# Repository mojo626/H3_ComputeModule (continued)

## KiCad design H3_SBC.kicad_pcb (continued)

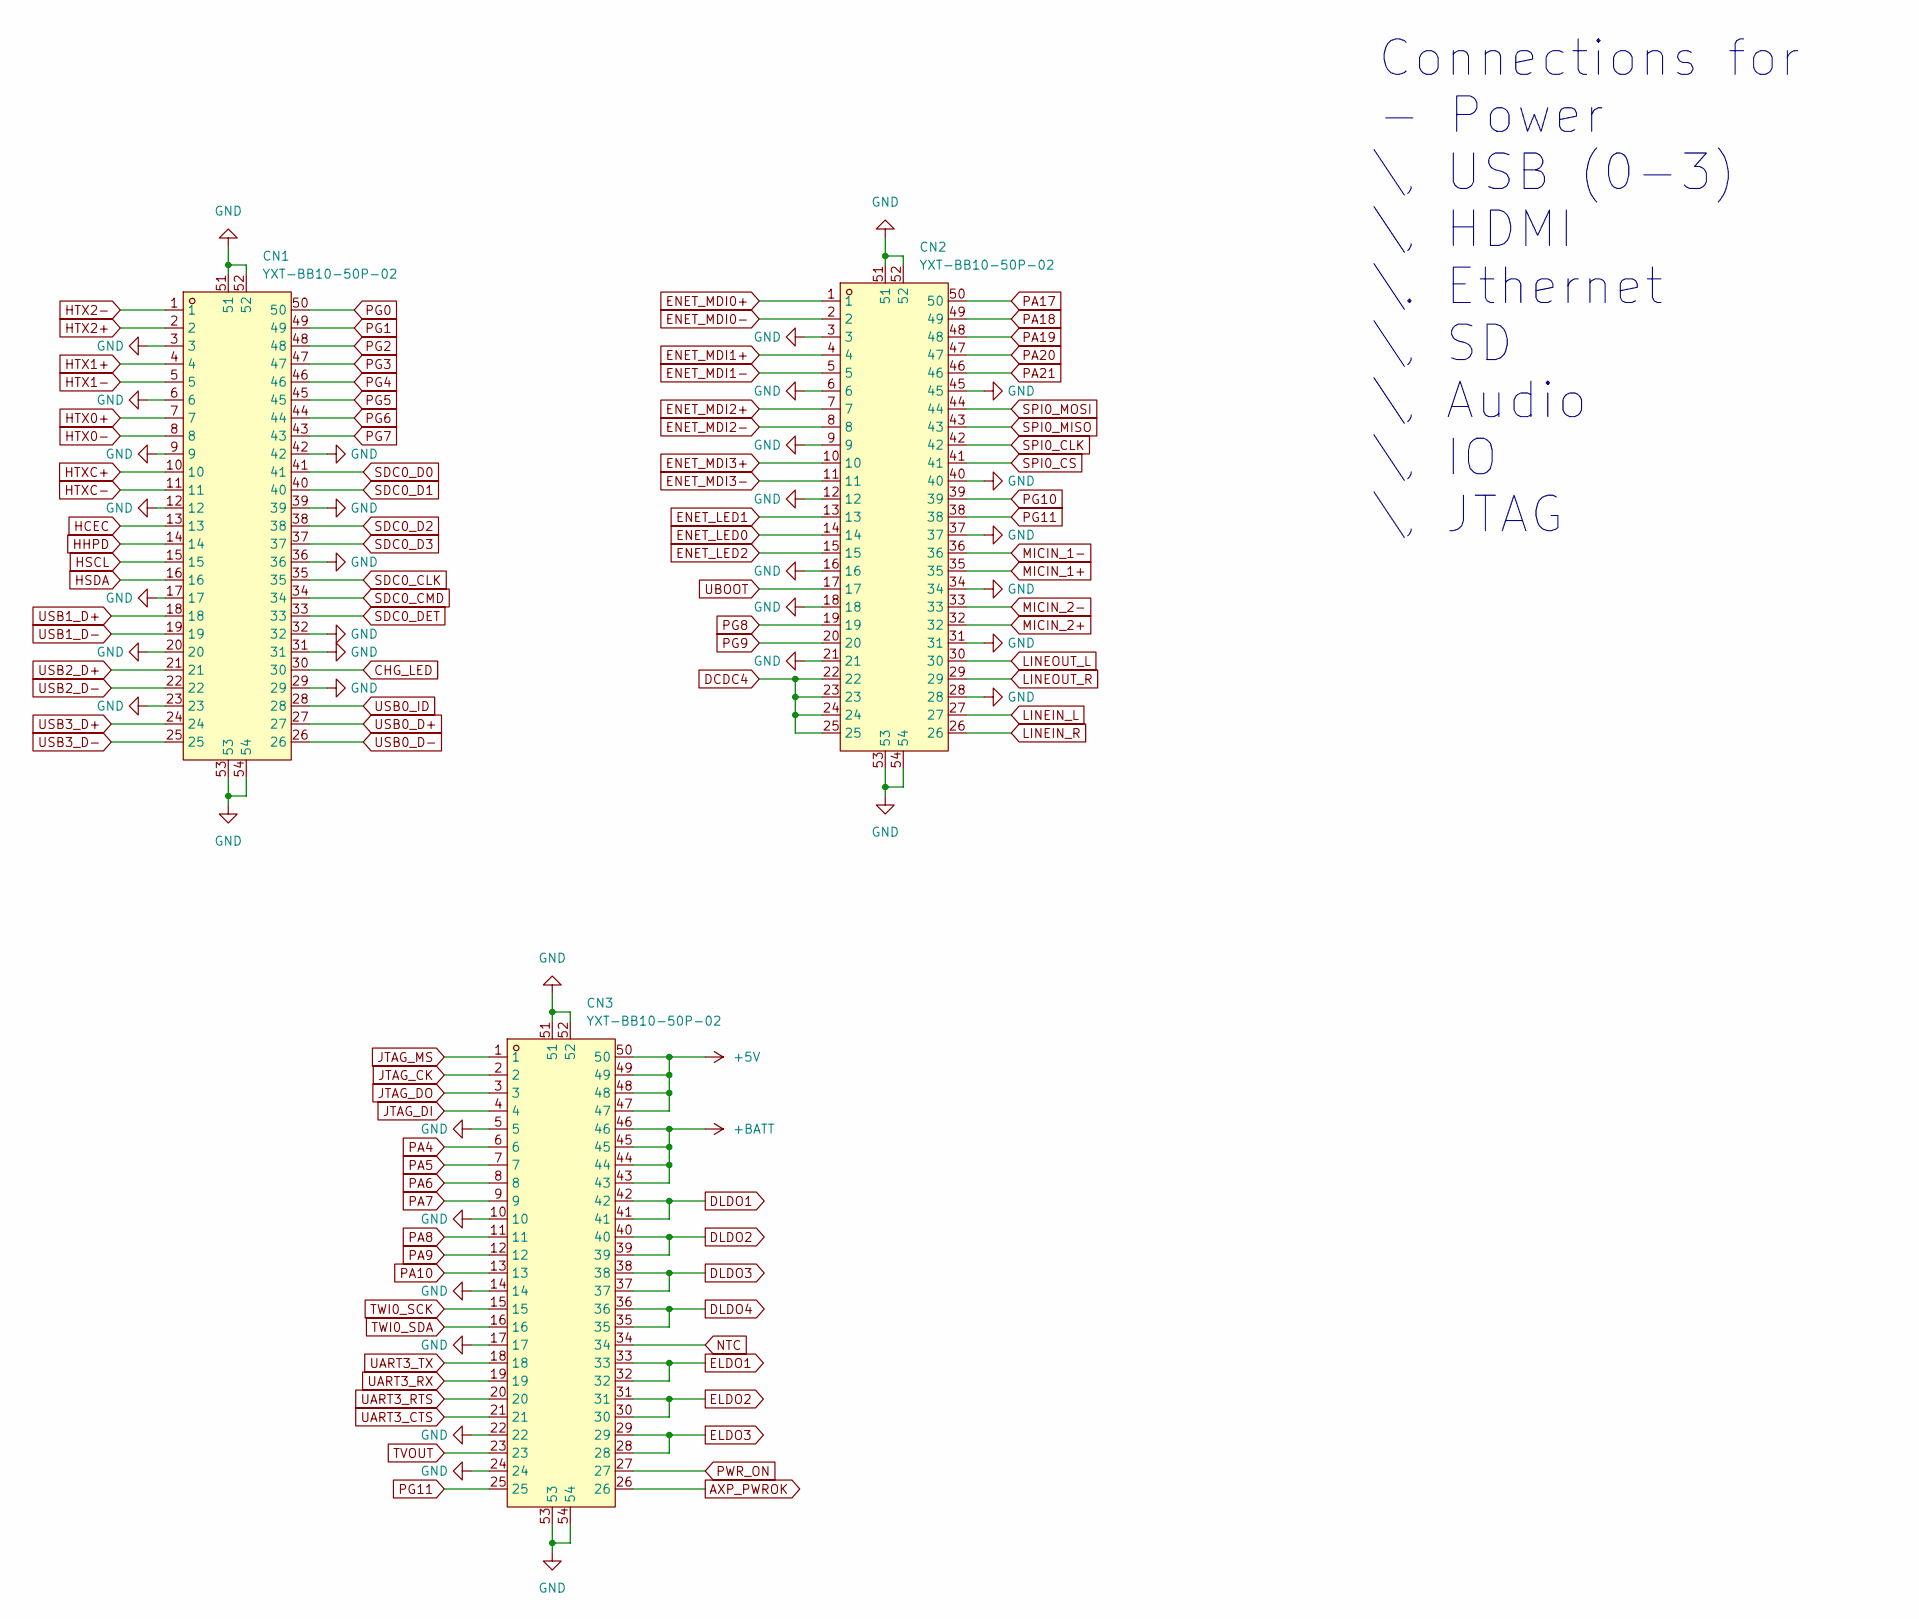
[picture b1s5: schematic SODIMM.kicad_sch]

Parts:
CN1, CN2, CN3: YXT-BB10-50P-02; CONN-SMD_YXT-BB10-50P-02; LCSC Part C2763977

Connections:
+5V: CN3.47, CN3.48, CN3.49, CN3.50; also elsewhere on the board
+BATT: CN3.43, CN3.44, CN3.45, CN3.46; also elsewhere on the board
AXP_PWROK: CN3.26; also elsewhere on the board
CHG_LED: CN1.30; also elsewhere on the board
DCDC4: CN2.22, CN2.23, CN2.24, CN2.25; also elsewhere on the board
DLDO1: CN3.41, CN3.42; also elsewhere on the board
DLDO2: CN3.39, CN3.40; also elsewhere on the board
DLDO3: CN3.37, CN3.38; also elsewhere on the board
DLDO4: CN3.35, CN3.36; also elsewhere on the board
ELDO1: CN3.32, CN3.33; also elsewhere on the board
ELDO2: CN3.30, CN3.31; also elsewhere on the board
ELDO3: CN3.28, CN3.29; also elsewhere on the board
ENET_LED0: CN2.14; also elsewhere on the board
ENET_LED1: CN2.13; also elsewhere on the board
ENET_LED2: CN2.15; also elsewhere on the board
ENET_MDI0+: CN2.1; also elsewhere on the board
ENET_MDI0-: CN2.2; also elsewhere on the board
ENET_MDI1+: CN2.4; also elsewhere on the board
ENET_MDI1-: CN2.5; also elsewhere on the board
ENET_MDI2+: CN2.7; also elsewhere on the board
ENET_MDI2-: CN2.8; also elsewhere on the board
ENET_MDI3+: CN2.10; also elsewhere on the board
ENET_MDI3-: CN2.11; also elsewhere on the board
GND: CN1.3, CN1.6, CN1.9, CN1.12, CN1.17, CN1.20, CN1.23, CN1.29, CN1.31, CN1.32, CN1.36, CN1.39, CN1.42, CN1.51, CN1.52, CN1.53, CN1.54, CN2.3, CN2.6, CN2.9, CN2.12, CN2.16, CN2.18, CN2.21, CN2.28, CN2.31, CN2.34, CN2.37, CN2.40, CN2.45, CN2.51, CN2.52, CN2.53, CN2.54, CN3.5, CN3.10, CN3.14, CN3.17, CN3.22, CN3.24, CN3.51, CN3.52, CN3.53, CN3.54; also elsewhere on the board
HCEC: CN1.13; also elsewhere on the board
HHPD: CN1.14; also elsewhere on the board
HSCL: CN1.15; also elsewhere on the board
HSDA: CN1.16; also elsewhere on the board
HTX0+: CN1.7; also elsewhere on the board
HTX0-: CN1.8; also elsewhere on the board
HTX1+: CN1.4; also elsewhere on the board
HTX1-: CN1.5; also elsewhere on the board
HTX2+: CN1.2; also elsewhere on the board
HTX2-: CN1.1; also elsewhere on the board
HTXC+: CN1.10; also elsewhere on the board
HTXC-: CN1.11; also elsewhere on the board
JTAG_CK: CN3.2; also elsewhere on the board
JTAG_DI: CN3.4; also elsewhere on the board
JTAG_DO: CN3.3; also elsewhere on the board
JTAG_MS: CN3.1; also elsewhere on the board
LINEIN_L: CN2.27; also elsewhere on the board
LINEIN_R: CN2.26; also elsewhere on the board
LINEOUT_L: CN2.30; also elsewhere on the board
LINEOUT_R: CN2.29; also elsewhere on the board
MICIN_1+: CN2.35; also elsewhere on the board
MICIN_1-: CN2.36; also elsewhere on the board
MICIN_2+: CN2.32; also elsewhere on the board
MICIN_2-: CN2.33; also elsewhere on the board
NTC: CN3.34; also elsewhere on the board
PA4: CN3.6; also elsewhere on the board
PA5: CN3.7; also elsewhere on the board
PA6: CN3.8; also elsewhere on the board
PA7: CN3.9; also elsewhere on the board
PA8: CN3.11; also elsewhere on the board
PA9: CN3.12; also elsewhere on the board
PA10: CN3.13; also elsewhere on the board
PA17: CN2.50; also elsewhere on the board
PA18: CN2.49; also elsewhere on the board
PA19: CN2.48; also elsewhere on the board
PA20: CN2.47; also elsewhere on the board
PA21: CN2.46; also elsewhere on the board
PG0: CN1.50; also elsewhere on the board
PG1: CN1.49; also elsewhere on the board
PG2: CN1.48; also elsewhere on the board
PG3: CN1.47; also elsewhere on the board
PG4: CN1.46; also elsewhere on the board
PG5: CN1.45; also elsewhere on the board
PG6: CN1.44; also elsewhere on the board
PG7: CN1.43; also elsewhere on the board
PG8: CN2.19; also elsewhere on the board
PG9: CN2.20; also elsewhere on the board
PG10: CN2.39; also elsewhere on the board
PG11: CN2.38, CN3.25; also elsewhere on the board
PWR_ON: CN3.27; also elsewhere on the board
SDC0_CLK: CN1.35; also elsewhere on the board
SDC0_CMD: CN1.34; also elsewhere on the board
SDC0_D0: CN1.41; also elsewhere on the board
SDC0_D1: CN1.40; also elsewhere on the board
SDC0_D2: CN1.38; also elsewhere on the board
SDC0_D3: CN1.37; also elsewhere on the board
SDC0_DET: CN1.33; also elsewhere on the board
SPI0_CLK: CN2.42; also elsewhere on the board
SPI0_CS: CN2.41; also elsewhere on the board
SPI0_MISO: CN2.43; also elsewhere on the board
SPI0_MOSI: CN2.44; also elsewhere on the board
TVOUT: CN3.23; also elsewhere on the board
TWI0_SCK: CN3.15; also elsewhere on the board
TWI0_SDA: CN3.16; also elsewhere on the board
UART3_CTS: CN3.21; also elsewhere on the board
UART3_RTS: CN3.20; also elsewhere on the board
UART3_RX: CN3.19; also elsewhere on the board
UART3_TX: CN3.18; also elsewhere on the board
UBOOT: CN2.17; also elsewhere on the board
USB0_D+: CN1.27; also elsewhere on the board
USB0_D-: CN1.26; also elsewhere on the board
USB0_ID: CN1.28; also elsewhere on the board
USB1_D+: CN1.18; also elsewhere on the board
USB1_D-: CN1.19; also elsewhere on the board
USB2_D+: CN1.21; also elsewhere on the board
USB2_D-: CN1.22; also elsewhere on the board
USB3_D+: CN1.24; also elsewhere on the board
USB3_D-: CN1.25; also elsewhere on the board

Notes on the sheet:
Connections for - Power \, USB (0-3) \, HDMI \. Ethernet \, SD \, Audio \, IO \, JTAG

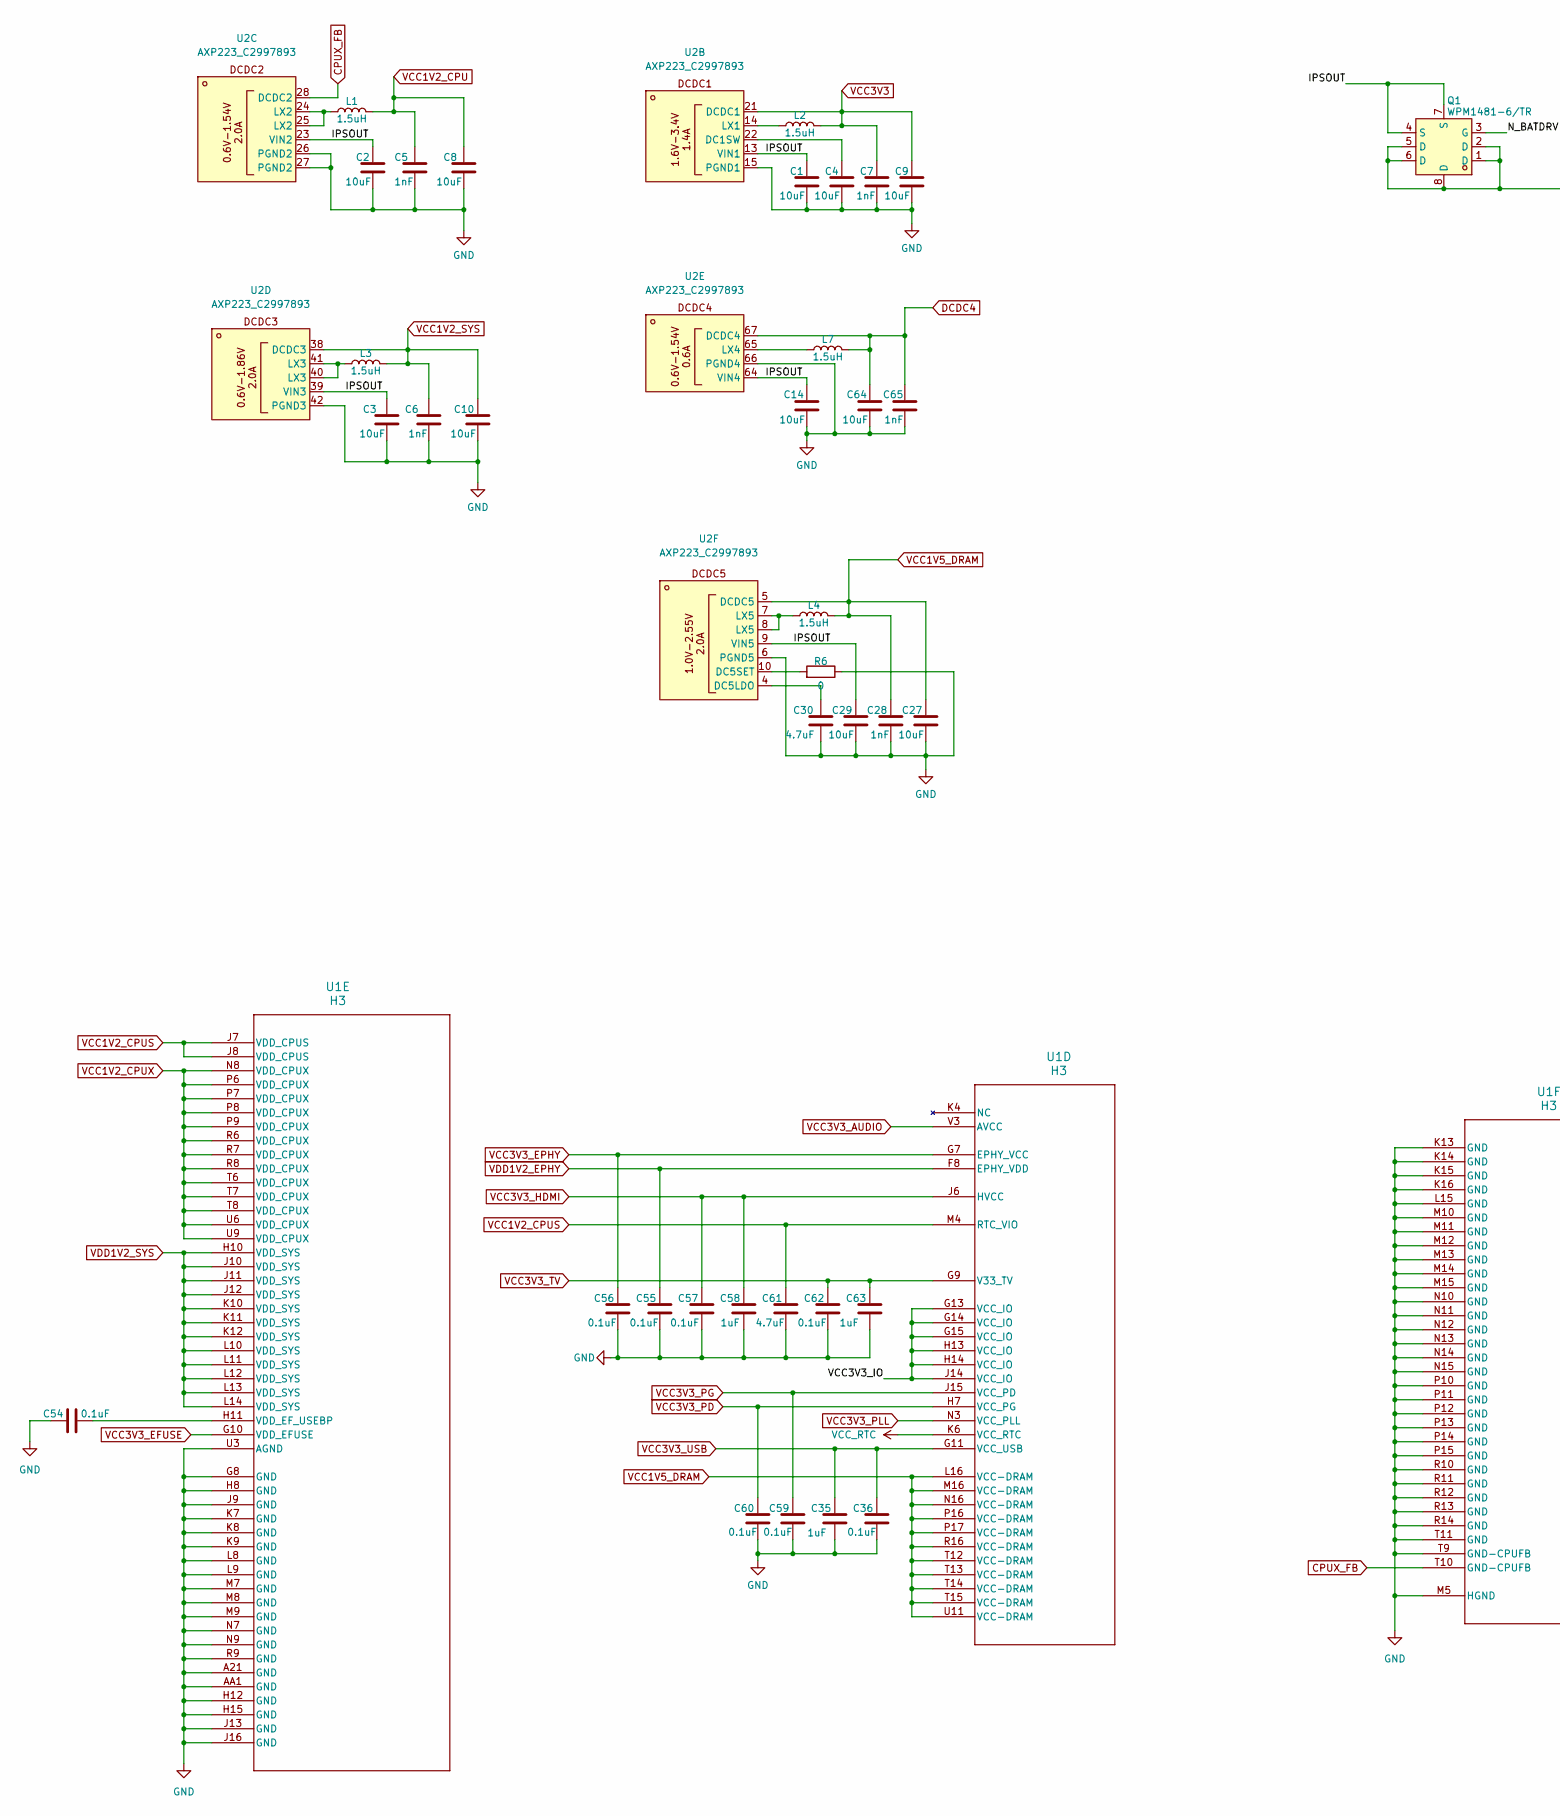
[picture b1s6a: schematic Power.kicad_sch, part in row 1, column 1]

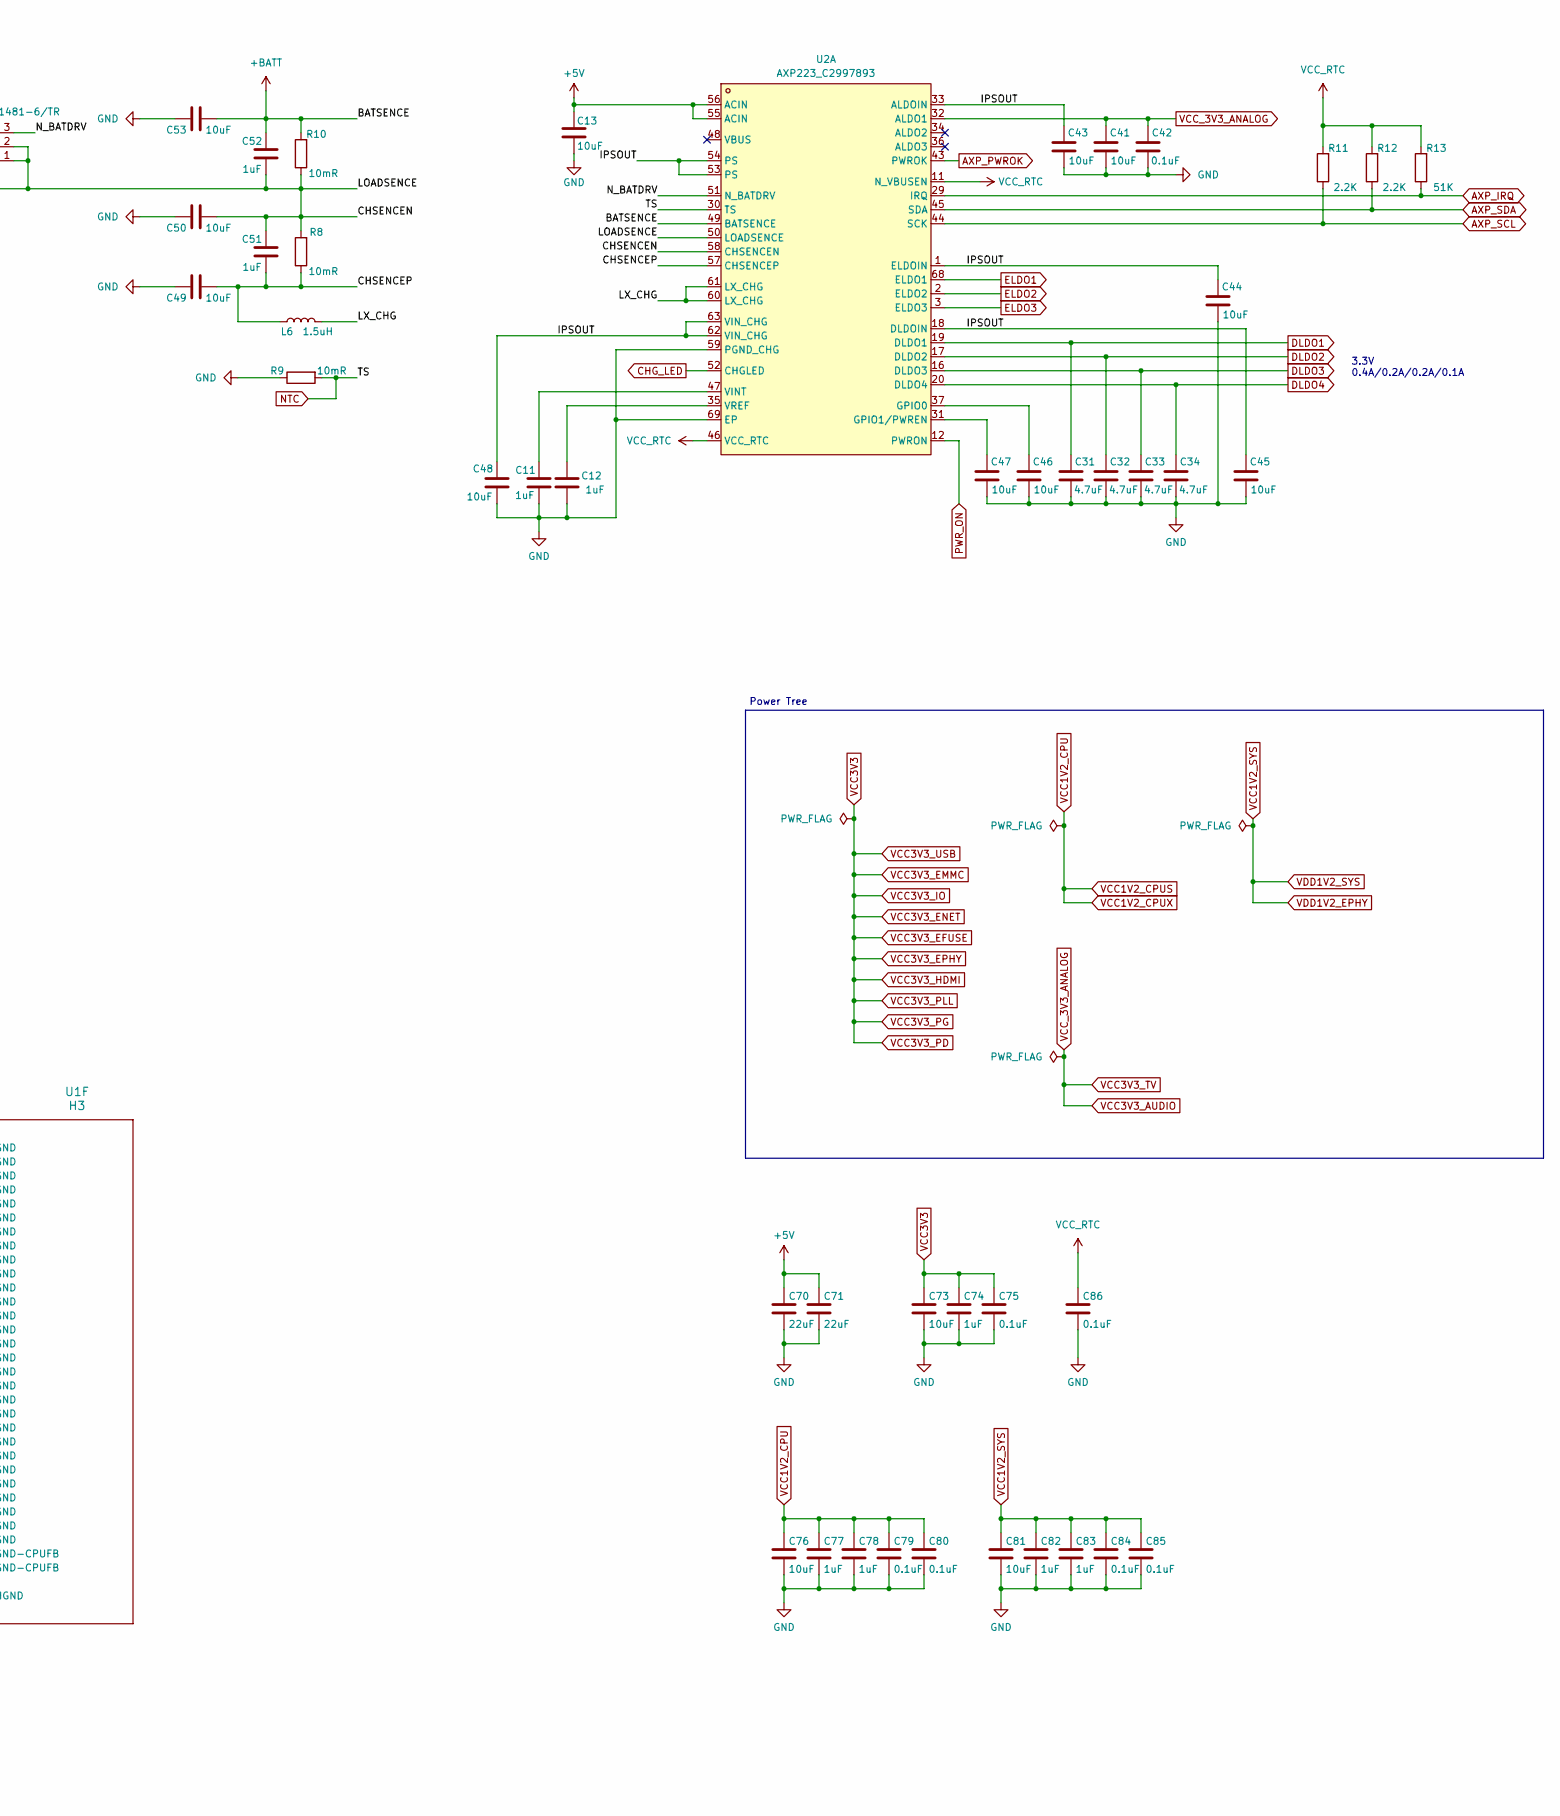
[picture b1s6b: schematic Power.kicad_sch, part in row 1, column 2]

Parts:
C1, C2, C3, C4, C8, C9, C10, C13, C14, C27, C29, C41, C43, C44, C45, C46, C47, C48, C49, C50, C53, C64, C73, C76, C81: 10uF; C_0402_1005Metric
C5, C6, C7, C28, C65: 1nF; C_0402_1005Metric
C11, C12, C35, C51, C52, C58, C63, C74, C77, C78, C82, C83: 1uF; C_0402_1005Metric
C30, C31, C32, C33, C34, C61: 4.7uF; C_0402_1005Metric
C36, C42, C54, C55, C56, C57, C59, C60, C62, C75, C79, C80, C84, C85, C86: 0.1uF; C_0402_1005Metric
C70, C71: 22uF; C_0603_1608Metric
L1, L2, L3, L4, L6, L7: 1.5uH; L_0402_1005Metric
Q1: WPM1481-6/TR; DFN-6L_L2.0-W2.0-P0.65-BL_WPM1481-6; LCSC Part C239798
R6: 0; R_0402_1005Metric
R8, R9, R10: 10mR; R_0402_1005Metric
R11, R12: 2.2K; R_0402_1005Metric
R13: 51K; R_0402_1005Metric
U1: H3; BGA-347_L14.0-W14.0-R21-C21-P0.65-TL
U2: AXP223_C2997893; QFN-68_L8.0-W8.0-P0.40-TL-EP5.7; LCSC Part C2997893

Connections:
+5V: C13.1, C70.1, C71.1, U2.55 (ACIN), U2.56 (ACIN); also elsewhere on the board
+BATT: C52.2, C53.1, R10.2, U2.49 (BATSENCE); also elsewhere on the board
/Power/CHSENCEN: C50.1, C51.2, C52.1, Q1.1 (D), Q1.2 (D), Q1.5 (D), Q1.6 (D), Q1.8 (D), R8.2, R10.1, U2.50 (LOADSENCE), U2.58 (CHSENCEN)
/Power/CHSENCEP: C49.2, C51.1, L6.1, R8.1, U2.57 (CHSENCEP)
/Power/IPSOUT: C1.2, C2.2, C3.2, C14.2, C29.2, C43.2, C44.2, C45.2, C48.2, Q1.4 (S), Q1.7 (S), U2.1 (ELDOIN), U2.9 (VIN5), U2.13 (VIN1), U2.18 (DLDOIN), U2.23 (VIN2), U2.33 (ALDOIN), U2.39 (VIN3), U2.53 (PS), U2.54 (PS), U2.62 (VIN_CHG), U2.63 (VIN_CHG), U2.64 (VIN4)
/Power/LX_CHG: L6.2, U2.60 (LX_CHG), U2.61 (LX_CHG)
/Power/N_BATDRV: Q1.3 (G), U2.51 (N_BATDRV)
AXP_IRQ: R13.1, U2.29 (IRQ); also elsewhere on the board
AXP_PWROK: U2.43 (PWROK); also elsewhere on the board
AXP_SCL: R11.1, U2.44 (SCK); also elsewhere on the board
AXP_SDA: R12.1, U2.45 (SDA); also elsewhere on the board
CHG_LED: U2.52 (CHGLED); also elsewhere on the board
CPUX_FB: U1.T10 (GND-CPUFB), U2.28 (DCDC2)
DCDC4: C64.2, C65.2, L7.2, U2.67 (DCDC4); also elsewhere on the board
DLDO1: C31.2, U2.19 (DLDO1); also elsewhere on the board
DLDO2: C32.2, U2.17 (DLDO2); also elsewhere on the board
DLDO3: C33.2, U2.16 (DLDO3); also elsewhere on the board
DLDO4: C34.2, U2.20 (DLDO4); also elsewhere on the board
ELDO1: U2.68 (ELDO1); also elsewhere on the board
ELDO2: U2.2 (ELDO2); also elsewhere on the board
ELDO3: U2.3 (ELDO3); also elsewhere on the board
GND: C1.1, C2.1, C3.1, C4.1, C5.1, C6.1, C7.1, C8.1, C9.1, C10.1, C11.2, C12.1, C13.2, C14.1, C27.1, C28.1, C29.1, C30.1, C31.1, C32.1, C33.1, C34.1, C35.1, C36.1, C41.1, C42.1, C43.1, C44.1, C45.1, C46.1, C47.1, C48.1, C49.1, C50.2, C53.2, C54.1, C55.1, C56.1, C57.1, C58.1, C59.1, C60.1, C61.1, C62.1, C63.1, C64.1, C65.1, C70.2, C71.2, C73.2, C74.2, C75.2, C76.2, C77.2, C78.2, C79.2, C80.2, C81.2, C82.2, C83.2, C84.2, C85.2, C86.2, R6.1, R9.1, U1.A21 (GND), U1.AA1 (GND), U1.G8 (GND), U1.H8 (GND), U1.H12 (GND), U1.H15 (GND), U1.J9 (GND), U1.J13 (GND), U1.J16 (GND), U1.K7 (GND), U1.K8 (GND), U1.K9 (GND), U1.K13 (GND), U1.K14 (GND), U1.K15 (GND), U1.K16 (GND), U1.L8 (GND), U1.L9 (GND), U1.L15 (GND), U1.M5 (HGND), U1.M7 (GND), U1.M8 (GND), U1.M9 (GND), U1.M10 (GND), U1.M11 (GND), U1.M12 (GND), U1.M13 (GND), U1.M14 (GND), U1.M15 (GND), U1.N7 (GND), U1.N9 (GND), U1.N10 (GND), U1.N11 (GND), U1.N12 (GND), U1.N13 (GND), U1.N14 (GND), U1.N15 (GND), U1.P10 (GND), U1.P11 (GND), U1.P12 (GND), U1.P13 (GND), U1.P14 (GND), U1.P15 (GND), U1.R9 (GND), U1.R10 (GND), U1.R11 (GND), U1.R12 (GND), U1.R13 (GND), U1.R14 (GND), U1.T9 (GND-CPUFB), U1.T11 (GND), U1.U3 (AGND), U2.6 (PGND5), U2.15 (PGND1), U2.26 (PGND2), U2.27 (PGND2), U2.42 (PGND3), U2.59 (PGND_CHG), U2.66 (PGND4), U2.69 (EP); also elsewhere on the board
NTC: R9.2, U2.30 (TS); also elsewhere on the board
unnamed: L1.1, U2.24 (LX2), U2.25 (LX2)
unnamed: L3.1, U2.40 (LX3), U2.41 (LX3)
unnamed: L4.1, U2.7 (LX5), U2.8 (LX5)
unnamed: C54.2, U1.H11 (VDD_EF_USEBP)
unnamed: C46.2, U2.37 (GPIO0)
unnamed: C47.2, U2.31 (GPIO1/PWREN)
unnamed: C11.1, U2.47 (VINT)
unnamed: C12.2, U2.35 (VREF)
unnamed: C4.2, U2.22 (DC1SW)
unnamed: L2.1, U2.14 (LX1)
unnamed: L7.1, U2.65 (LX4)
unnamed: C30.2, U2.4 (DC5LDO)
unnamed: R6.2, U2.10 (DC5SET)
PWR_ON: U2.12 (PWRON); also elsewhere on the board
VCC1V2_CPU: C5.2, C8.2, C61.2, C76.1, C77.1, C78.1, C79.1, C80.1, L1.2, U1.J7 (VDD_CPUS), U1.J8 (VDD_CPUS), U1.M4 (RTC_VIO), U1.N8 (VDD_CPUX), U1.P6 (VDD_CPUX), U1.P7 (VDD_CPUX), U1.P8 (VDD_CPUX), U1.P9 (VDD_CPUX), U1.R6 (VDD_CPUX), U1.R7 (VDD_CPUX), U1.R8 (VDD_CPUX), U1.T6 (VDD_CPUX), U1.T7 (VDD_CPUX), U1.T8 (VDD_CPUX), U1.U6 (VDD_CPUX), U1.U9 (VDD_CPUX)
VCC1V2_SYS: C6.2, C10.2, C55.2, C81.1, C82.1, C83.1, C84.1, C85.1, L3.2, U1.F8 (EPHY_VDD), U1.H10 (VDD_SYS), U1.J10 (VDD_SYS), U1.J11 (VDD_SYS), U1.J12 (VDD_SYS), U1.K10 (VDD_SYS), U1.K11 (VDD_SYS), U1.K12 (VDD_SYS), U1.L10 (VDD_SYS), U1.L11 (VDD_SYS), U1.L12 (VDD_SYS), U1.L13 (VDD_SYS), U1.L14 (VDD_SYS), U2.38 (DCDC3)
VCC1V5_DRAM: C27.2, C28.2, L4.2, U1.L16 (VCC-DRAM), U1.M16 (VCC-DRAM), U1.N16 (VCC-DRAM), U1.P16 (VCC-DRAM), U1.P17 (VCC-DRAM), U1.R16 (VCC-DRAM), U1.T12 (VCC-DRAM), U1.T13 (VCC-DRAM), U1.T14 (VCC-DRAM), U1.T15 (VCC-DRAM), U1.U11 (VCC-DRAM), U2.5 (DCDC5); also elsewhere on the board
VCC3V3: C7.2, C9.2, C35.2, C36.2, C56.2, C57.2, C58.2, C59.2, C60.2, C73.1, C74.1, C75.1, L2.2, U1.G7 (EPHY_VCC), U1.G10 (VDD_EFUSE), U1.G11 (VCC_USB), U1.G13 (VCC_IO), U1.G14 (VCC_IO), U1.G15 (VCC_IO), U1.H7 (VCC_PG), U1.H13 (VCC_IO), U1.H14 (VCC_IO), U1.J6 (HVCC), U1.J14 (VCC_IO), U1.J15 (VCC_PD), U1.N3 (VCC_PLL), U2.21 (DCDC1); also elsewhere on the board
VCC3V3_AUDIO: C41.2, C42.2, C62.2, C63.2, U1.G9 (V33_TV), U1.V3 (AVCC), U2.32 (ALDO1)
VCC_RTC: C86.1, R11.2, R12.2, R13.2, U1.K6 (VCC_RTC), U2.11 (N_VBUSEN), U2.46 (VCC_RTC); also elsewhere on the board

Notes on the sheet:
3.3V 0.4A/0.2A/0.2A/0.1A
Power Tree

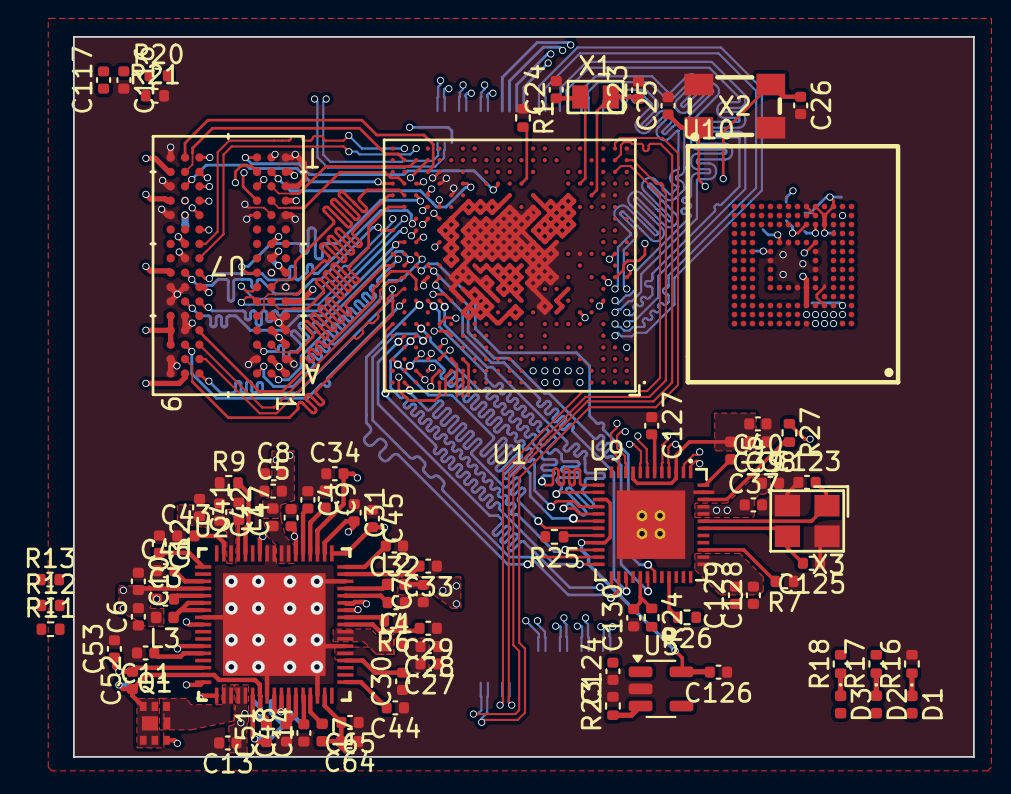
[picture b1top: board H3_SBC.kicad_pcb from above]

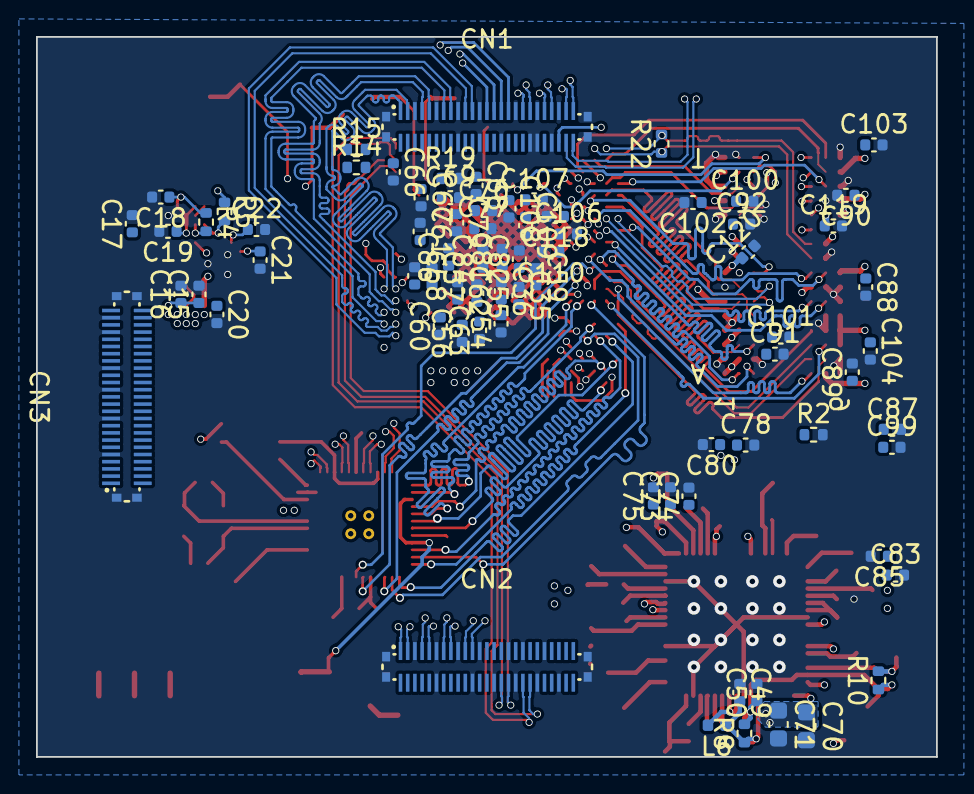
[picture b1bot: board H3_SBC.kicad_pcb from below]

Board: 6 copper layers, 50.0 x 40.0 mm, 164 parts (75 on the bottom side), 236 nets.

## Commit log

2025-03-29 changed some ethernet stuff
2025-03-30 switched eMMC
2025-04-02 power changes
2025-04-02 power changes and pinout update
2025-04-03 minor changes
2025-04-03 power things, minor changes
2025-04-04 small changes
2025-04-06 some backups
2025-04-06 recovered ethernet power changes
2025-04-06 small fixes
2025-04-06 linking symbols to footprints
2025-04-07 placed major components
2025-04-08 placing capacitors
2025-04-08 moved some more capacitors
2025-04-11 started RAM routing, might move to 1 module though
2025-04-11 switched to one RAM module
2025-04-16 RAM routing additions
2025-04-16 power routing additions
2025-04-17 ethernet start and length tuning
2025-04-17 more tuning changes
2025-04-17 routed ethernet and emmc data lines
2025-04-22 placed all decaps, emmc routing changes, DDR routing changes
